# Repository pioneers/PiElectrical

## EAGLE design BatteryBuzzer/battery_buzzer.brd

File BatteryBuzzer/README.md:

#Battery Buzzer

Reacts the how angry the battery is

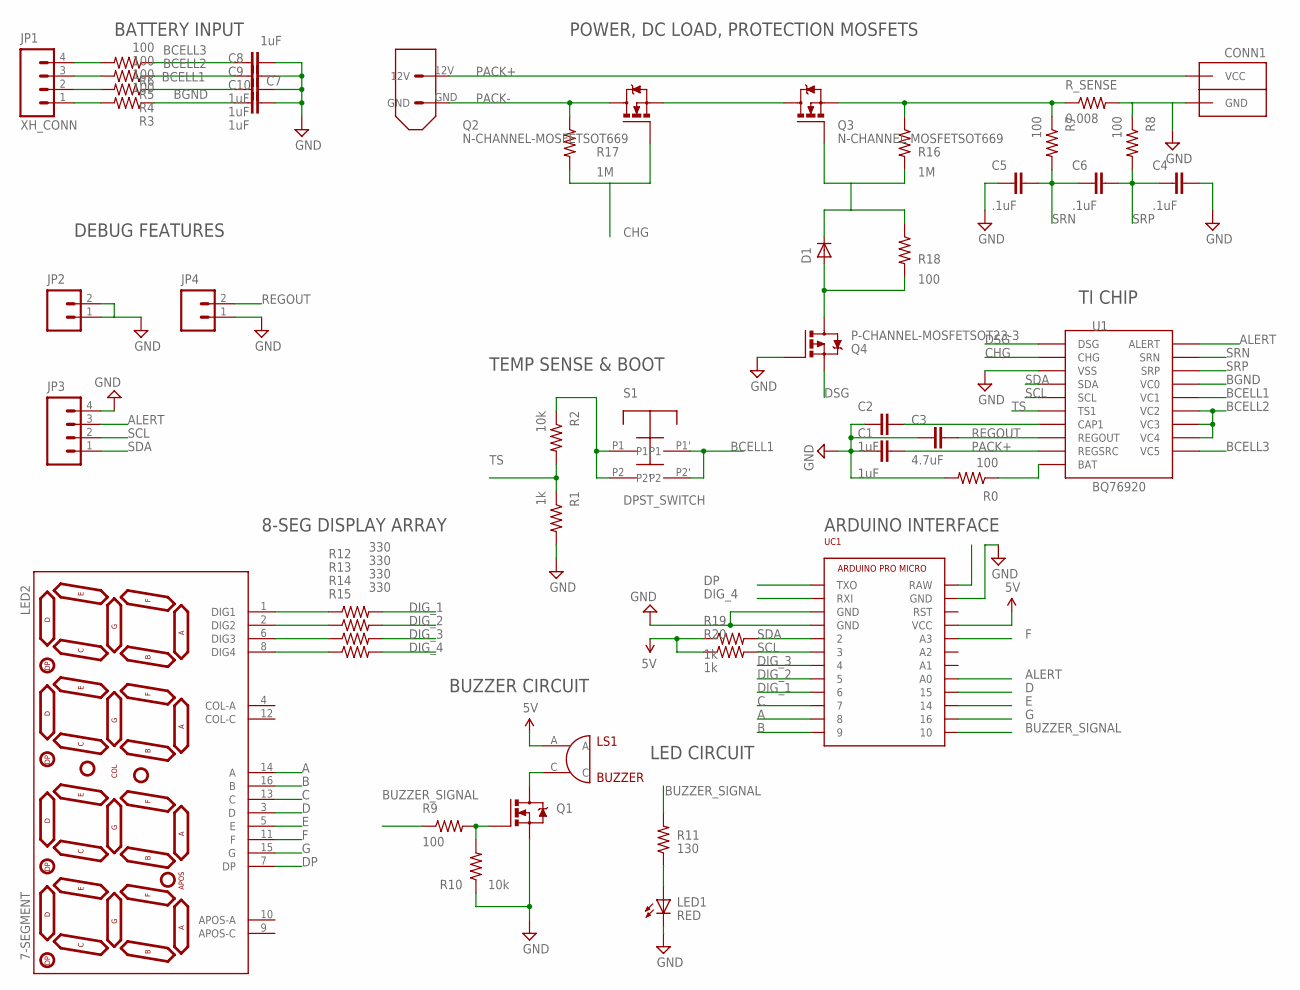
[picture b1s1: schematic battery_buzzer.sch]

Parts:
C1, C2, C7, C8, C9, C10: 1uF; 0603-CAP
C3: 4.7uF; 0603-CAP
C4, C5, C6: .1uF; 0603-CAP
CONN1: ANDERSONVERTICAL; ANDERSON_VERTICAL
D1: DIODESOD-323; SOD-323
JP1: XH_CONN; XH_CONNECTOR_4POS_2.5MM
JP2, JP4: M02PTH; 1X02
JP3: M04PTH; 1X04
LED1: RED; LED-0805
LED2: 7-SEGMENT; 7-SEGMENT-4DIGIT-YOUNGSUN
LS1: BUZZER; BUZZER_MAGNETIC_5V_12MM_RADIAL
Q1: IRFML8244; SOT23-3
Q2, Q3: N-CHANNEL-MOSFETSOT669; SOT669
Q4: P-CHANNEL-MOSFETSOT23-3; SOT23-3
R0, R3, R4, R5, R6, R7, R8, R9, R18: 100; R0603
R1, R19, R20: 1k; R0603
R2, R10: 10k; R0603
R11: 130; R0603
R12, R13, R14, R15: 330; R0603
R16, R17: 1M; R0603
R_SENSE: 0.008; V235/17
S1: DPST_SWITCH; C&K_SWITCH
U1: BQ76920; 20-TSSOP
U$1: XT60CONNECTOR
UC1: ARDUINO_PRO_MICRO

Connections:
5V: LS1.A, R19.1, R20.1, UC1.VCC
A: LED2.14 (A), UC1.8
ALERT: JP3.3, U1.P$20 (ALERT), UC1.A0
B: LED2.16 (B), UC1.9
BCELL1: C9.1, R4.1, S1.P1', S1.P2', U1.P$16 (VC1)
BCELL2: C8.1, R5.1, U1.P$13 (VC4), U1.P$14 (VC3), U1.P$15 (VC2)
BCELL3: C7.2, R6.1, U1.P$12 (VC5)
BGND: C10.1, R3.1, U1.P$17 (VC0)
BUZZER_SIGNAL: R9.1, R11.2, UC1.10
C: LED2.13 (C), UC1.7
CHG: Q2.4 (G), R17.2, U1.P$2 (CHG)
D: LED2.3 (D), UC1.15
DIG_1: R12.2, UC1.6
DIG_2: R13.2, UC1.5
DIG_3: R14.2, UC1.4
DIG_4: R15.2, UC1.RXI
DP: LED2.7 (DP), UC1.TXO
DSG: Q4.2 (S), U1.P$1 (DSG)
E: LED2.5 (E), UC1.14
F: LED2.11 (F), UC1.A3
G: LED2.15 (G), UC1.16
GND: C1.1, C2.1, C3.1, C4.2, C5.1, C7.1, C8.2, C9.2, C10.2, CONN1.PIN1 (GND), JP2.1, JP2.2, JP3.4, JP4.1, LED1.C, Q1.2 (S), Q4.1 (G), R0.2, R1.2, R8.1, R10.1, R_SENSE.2, U1.P$3 (VSS), UC1.GND@0 (GND), UC1.GND@1 (GND), UC1.GND@2 (GND)
unnamed: R0.1, U1.P$10 (BAT)
unnamed: C2.2, U1.P$7 (CAP1)
unnamed: JP1.1, R3.2
unnamed: JP1.2, R4.2
unnamed: LS1.C, Q1.3 (D)
unnamed: Q1.1 (G), R9.2, R10.2
unnamed: LED1.A, R11.1
unnamed: R2.1, S1.P1, S1.P2
unnamed: LED2.1 (DIG1), R12.1
unnamed: JP1.3, R5.2
unnamed: LED2.2 (DIG2), R13.1
unnamed: JP1.4, R6.2
unnamed: LED2.6 (DIG3), R14.1
unnamed: Q2.1 (S), Q2.2 (S), Q2.3 (S), Q3.MB (D)
unnamed: LED2.8 (DIG4), R15.1
unnamed: Q3.1 (S), Q3.2 (S), Q3.3 (S), R7.1, R16.1, R_SENSE.1
unnamed: D1.1 (A), Q4.3 (D), R18.2
unnamed: D1.2 (C), Q3.4 (G), R16.2, R18.1
PACK+: C1.2, CONN1.PIN2 (VCC), U1.P$9 (REGSRC), U$1.12V
PACK-: Q2.MB (D), R17.1, U$1.GND
RAW: UC1.RAW
REGOUT: C3.2, JP4.2, U1.P$8 (REGOUT)
SCL: JP3.2, R20.2, U1.P$5 (SCL), UC1.3
SDA: JP3.1, R19.2, U1.P$4 (SDA), UC1.2
SRN: C5.2, C6.1, R7.2, U1.P$19 (SRN)
SRP: C4.1, C6.2, R8.2, U1.P$18 (SRP)
TS: R1.1, R2.2, U1.P$6 (TS1)

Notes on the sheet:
ARDUINO INTERFACE
LED CIRCUIT
BUZZER CIRCUIT
BATTERY INPUT
8-SEG DISPLAY ARRAY
DEBUG FEATURES
TEMP SENSE & BOOT
POWER, DC LOAD, PROTECTION MOSFETS
TI CHIP

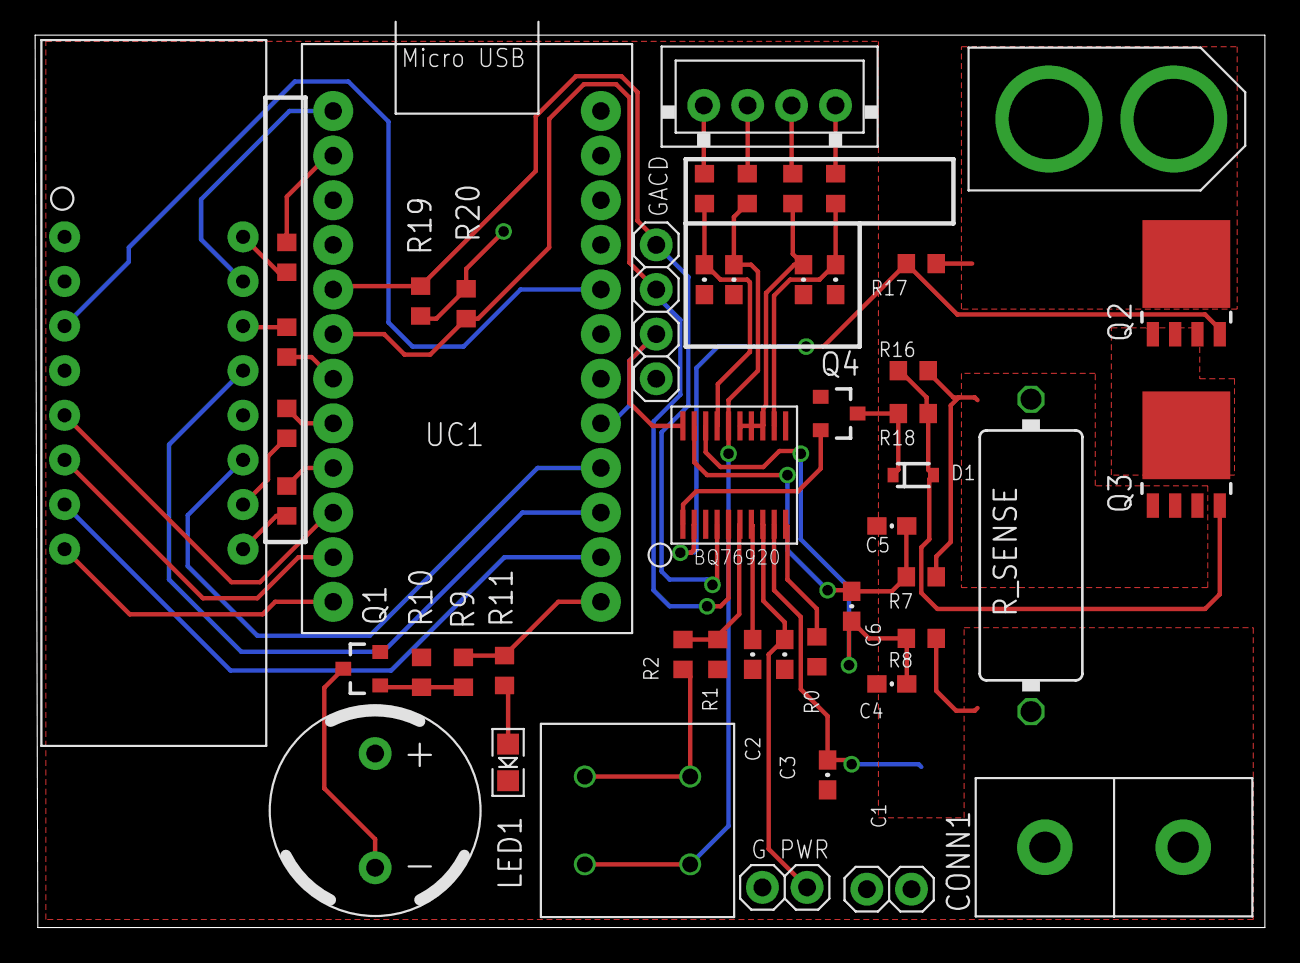
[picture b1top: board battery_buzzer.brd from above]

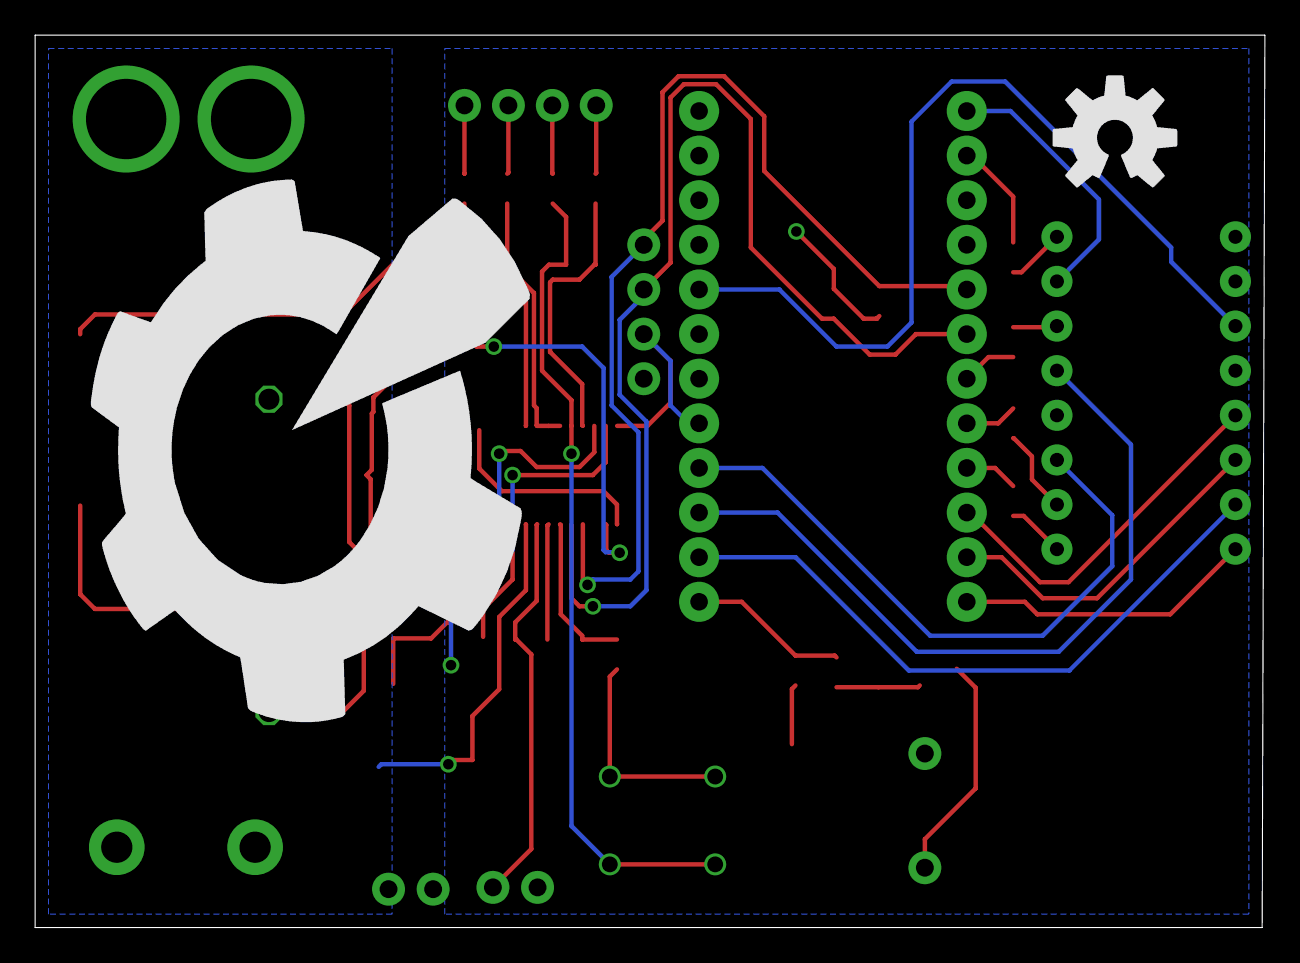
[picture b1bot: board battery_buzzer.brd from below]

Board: 2 copper layers, 70.0 x 50.8 mm, 51 parts (2 on the bottom side), 48 nets.

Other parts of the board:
U$2: OSHW-LOGO-L
U$4: PIE-LOGO

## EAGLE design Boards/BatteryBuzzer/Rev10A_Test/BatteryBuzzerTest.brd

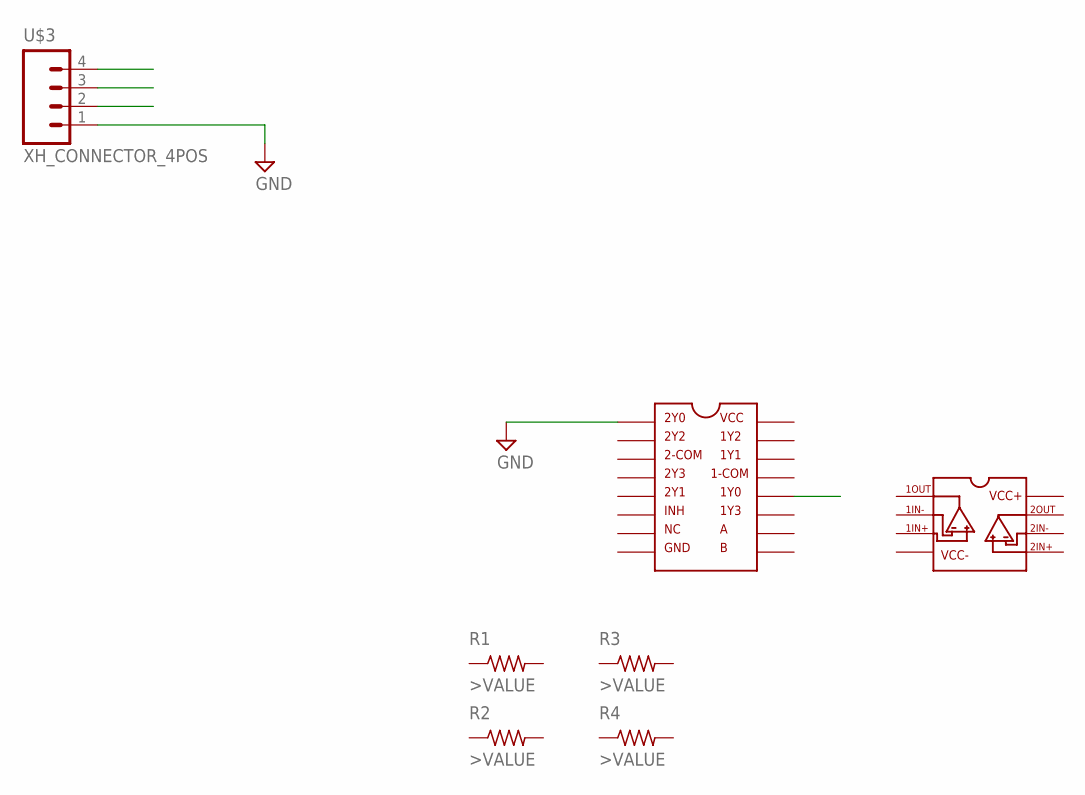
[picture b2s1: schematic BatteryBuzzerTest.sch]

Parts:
R1, R2, R3, R4: >VALUE; R0603
U$1: SN74HC4852; DIL16
U$2: TL072; DIL08
U$3: XH_CONNECTOR_4POS; XH_CONNECTOR_4POS_2.5MM

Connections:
BCELL1: U$1.12 (1Y0), U$3.2
BCELL2: U$3.3
BCELL3: U$3.4
GND: U$1.1 (2Y0), U$3.1

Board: 2 copper layers, 7 parts (0 on the bottom side), 2 nets, no tracks yet.

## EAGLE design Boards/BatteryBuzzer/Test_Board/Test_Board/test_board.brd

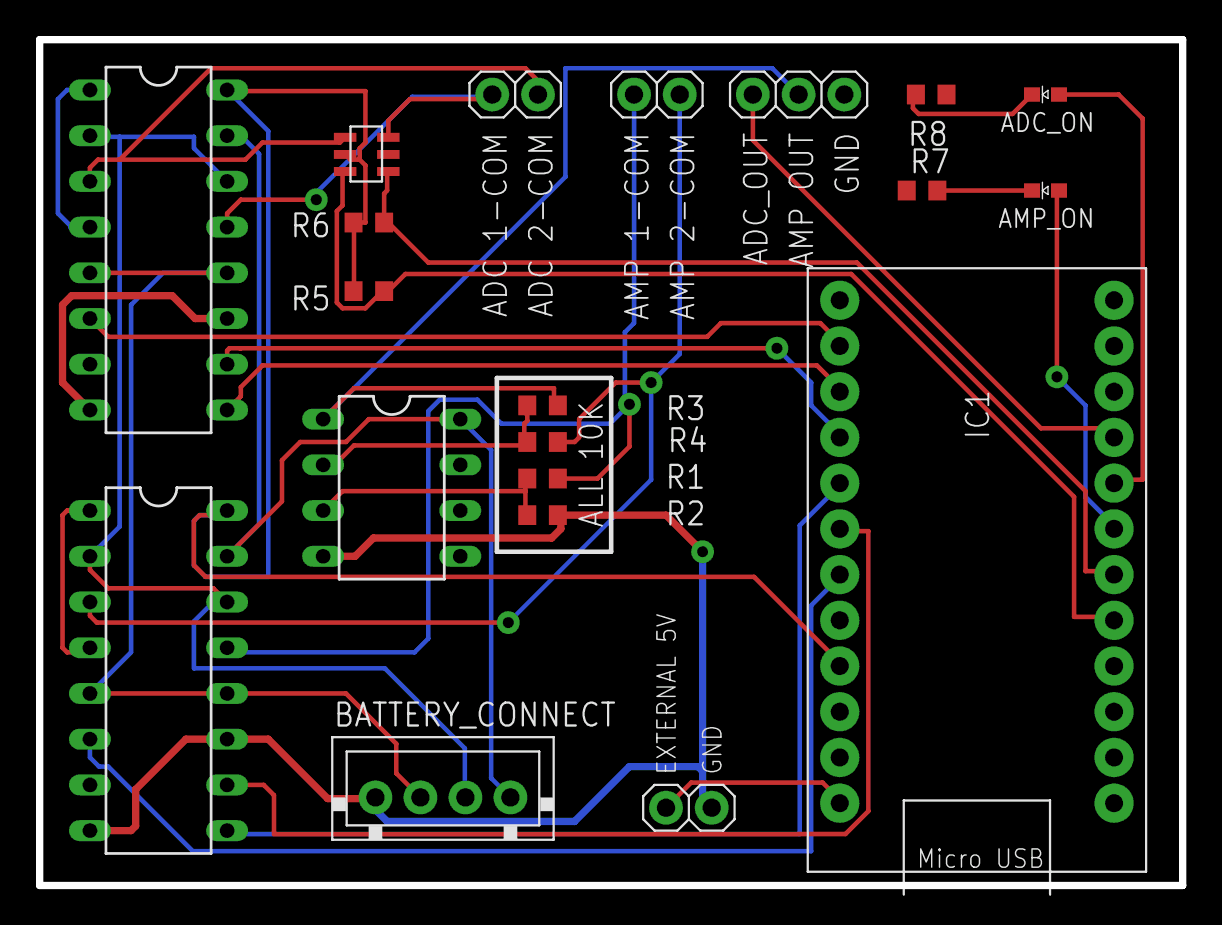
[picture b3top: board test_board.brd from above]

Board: 2 copper layers, 63.5 x 47.0 mm, 21 parts (1 on the bottom side), 26 nets.

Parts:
ADC_INPUTS: 1X02
ADC_ON: GREEN; LED-0603
AMP_ON: GREEN; LED-0603
BATTERY_CONNECT: XH_CONNECTOR_4POS; XH_CONNECTOR_4POS_2.5MM
EXTERNAL_POWER: 1X02
IC1: ARDUINO_PRO_MICRO
MUX_INPUTS: 1X02
OUTPUT: 1X03
R1, R2, R3, R4, R5, R6: 10k; R0603
R7, R8: 330; R0603
U$1, U$5: SN74HC4852; DIL16
U$2: TL072; DIL08
U$3: SOT-23_6PIN
U$7: PIE-LOGO-SMALL

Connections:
1-COM: MUX_INPUTS.2, R1.1, U$1.13
2-COM: MUX_INPUTS.1, R4.2, U$1.3
5V: EXTERNAL_POWER.2, IC1.RAW
A: IC1.A1, U$1.10
ADC_1-COM: ADC_INPUTS.2, U$3.P$1, U$5.13
ADC_2-COM: ADC_INPUTS.1, U$3.P$4, U$5.3
ADC_A: IC1.15, U$5.10
ADC_B: IC1.14, U$5.9
ADC_INH: IC1.16, U$5.6
ADC_OUT: IC1.6, OUTPUT.3
AMP_OUT: OUTPUT.2, R3.1, U$2.1
B: IC1.A0, U$1.9
BCELL1: BATTERY_CONNECT.2, U$1.5, U$1.12, U$5.5, U$5.12
BCELL2: BATTERY_CONNECT.3, U$1.2, U$1.14, U$5.2, U$5.14
BCELL3: BATTERY_CONNECT.4, U$1.15, U$2.8, U$5.15
GND: BATTERY_CONNECT.1, EXTERNAL_POWER.1, IC1.GND@0, IC1.GND@1, IC1.GND@2, OUTPUT.1, R2.1, R7.1, R8.1, U$1.1, U$1.4, U$1.8, U$1.11, U$2.4, U$3.P$2, U$5.1, U$5.4, U$5.8, U$5.11
INH_CONTROL: IC1.A2, U$1.6
LED_1: AMP_ON.A, IC1.4
LED_2: ADC_ON.A, IC1.5
unnamed: R1.2, R2.2, U$2.3
unnamed: R3.2, R4.1, U$2.2
unnamed: ADC_ON.C, R8.2
unnamed: AMP_ON.C, R7.2
SCL: IC1.3, R6.1, U$3.P$3
SDA: IC1.2, R5.1, U$3.P$6
VCC: IC1.VCC, R5.2, R6.2, U$1.16, U$3.P$5, U$5.16

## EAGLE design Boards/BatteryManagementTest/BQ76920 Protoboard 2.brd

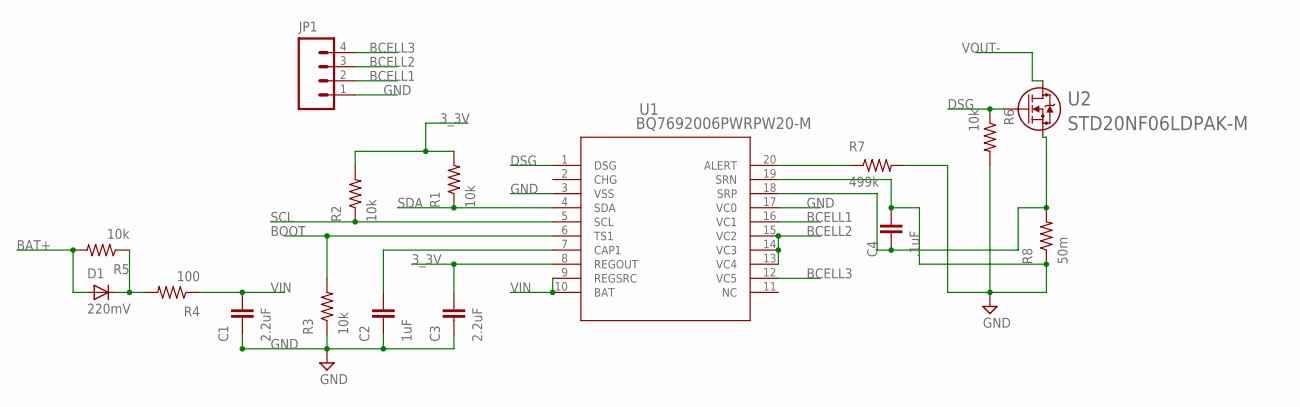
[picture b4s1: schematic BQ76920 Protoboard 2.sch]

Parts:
C1, C3: 2.2uF; 0603-CAP
C2: 1uF; 0603-CAP
C4: .1uF; 0603-CAP
D1: 220mV; SOD-323
JP1: M041X04-MTA; 1X04-MTA
R1, R2, R3, R5, R6: 10k; R0603
R4: 100; R0603
R7: 499k; R0603
R8: 50m; R2512
U1: BQ7692006PWRPW20-M; PW20-M
U2: STD20NF06LDPAK-M; DPAK-M

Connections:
3_3V: C3.2, R1.2, R2.2, U1.8 (REGOUT)
ALERT: R7.1, U1.20 (ALERT)
BAT+: D1.1 (A), R5.2
BCELL1: JP1.2, U1.16 (VC1)
BCELL2: JP1.3, U1.13 (VC4), U1.14 (VC3), U1.15 (VC2)
BCELL3: JP1.4, U1.12 (VC5)
BOOT: R3.2, U1.6 (TS1)
CAP1: C2.2, U1.7 (CAP1)
DSG: R6.1, U1.1 (DSG), U2.1
GND: C1.1, C2.1, C3.1, C4.2, JP1.1, R3.1, R6.2, R7.2, R8.1, U1.3 (VSS), U1.17 (VC0), U1.19 (SRN)
unnamed: D1.2 (C), R4.2, R5.1
SCL: R2.1, U1.5 (SCL)
SDA: R1.1, U1.4 (SDA)
SOURCE: C4.1, R8.2, U1.18 (SRP), U2.2 (3)
VIN: C1.2, R4.1, U1.9 (REGSRC), U1.10 (BAT)
VOUT-: U2.3 (2)

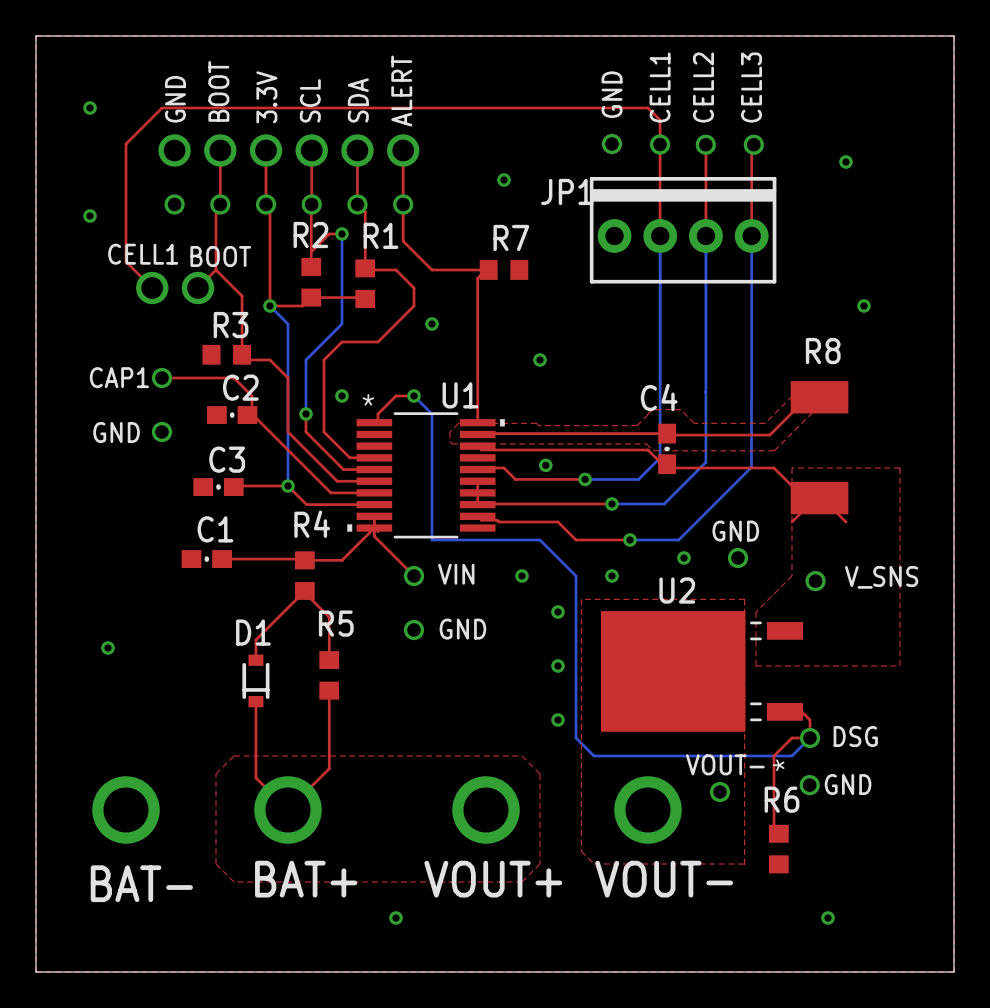
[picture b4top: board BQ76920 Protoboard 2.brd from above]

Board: 2 copper layers, 51.0 x 52.0 mm, 16 parts (0 on the bottom side), 15 nets.

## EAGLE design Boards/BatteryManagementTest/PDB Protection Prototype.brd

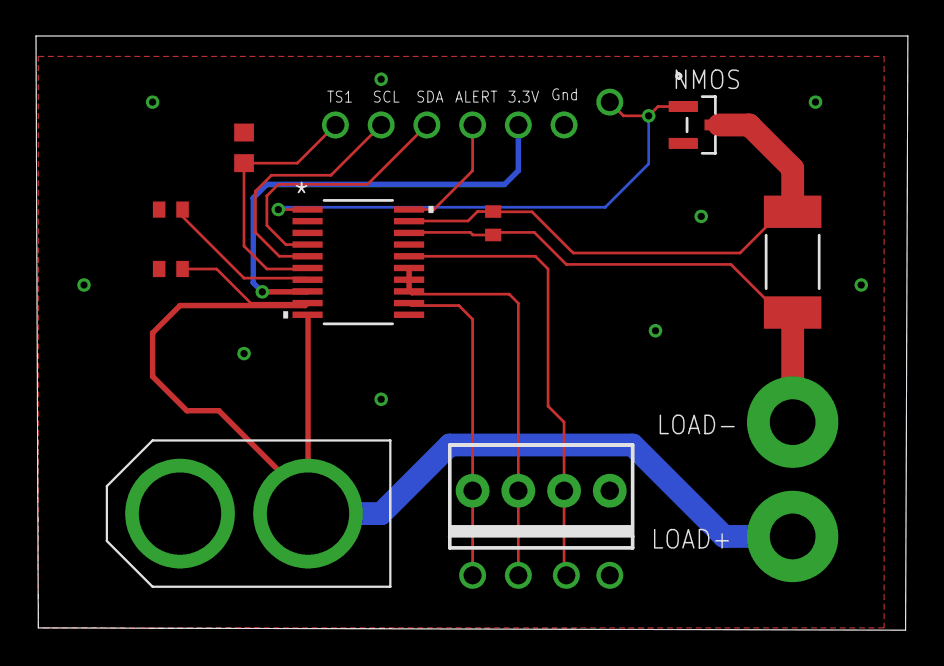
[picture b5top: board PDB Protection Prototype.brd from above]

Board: 2 copper layers, 48.4 x 33.0 mm, 9 parts (0 on the bottom side), 10 nets.

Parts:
C1, C2: 1uF; C0402
C3: .1uF; C0402
JP1: 1X04-MTA
R_SHUNT: 70m; R2512
R_TS: 10k; R0603
U1: BQ7692000PWR; PW20
U2: DMN6140L-13SOT-23-M; SOT-23-M
U$1: XT60CONNECTOR

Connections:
BCELL1: JP1.2, U1.16
BCELL2: JP1.3, U1.13, U1.14, U1.15
BCELL3: JP1.4, U1.12
DSG: U1.1, U2.1
GND: C1.2, C2.2, JP1.1, R_TS.1, U1.3, U1.17, U2.2, U$1.GND
LOAD-: C3.1, R_SHUNT.1, U1.18
unnamed: C3.2, R_SHUNT.2, U1.19, U2.3
unnamed: C1.1, U1.7
TS1: R_TS.2, U1.6
VBAT: C2.1, U1.9, U1.10, U$1.12V

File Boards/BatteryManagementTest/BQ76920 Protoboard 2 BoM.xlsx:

Reference Designator | Description | Manufacturer | Manufacturer Part Number | Distributor | Distributor Part Number
U1 | Battery Protection IC | Texas Instruments | BQ7692006PWR | Digikey | 296-39960-1-ND
C1, C2 | 1uF Capacitor
C3 | .1uF Capacitor |  | CL05A104MP5NNNC | Digikey | 1276-1443-1-ND
R_SHUNT | 5m Shunt | Bourns Inc. | CRE2512-FZ-R005E-3 | Digikey | CRE2512-FZ-R005E-3CT-ND
U2 | Power N-Channel Mosfet | STMicroelectronics | STD20NF06LAG | Digikey | 497-17143-1-ND

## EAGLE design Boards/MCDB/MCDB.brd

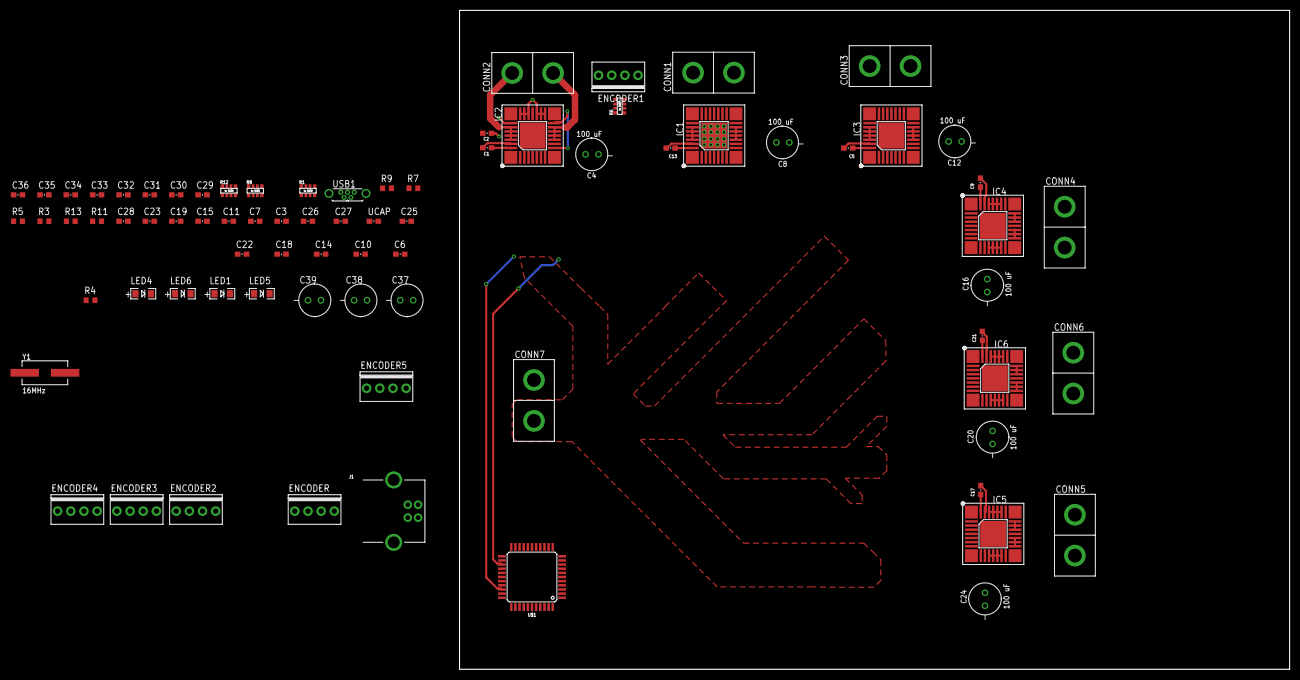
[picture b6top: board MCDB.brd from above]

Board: 2 copper layers, 160.0 x 127.0 mm, 78 parts (0 on the bottom side), 63 nets.

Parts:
C1, C5, C9, C13, C17, C21: 33 nF; 0603-CAP
C2, C6, C10, C14, C18, C22: 100 nF; 0603-CAP
C3, C7, C11, C15, C19, C23, C28: 1 uF; 0603-CAP
C4, C8, C12, C16, C20, C24: 100 uF; .248"CAP_THRU
C25: 22 pF; 0603-CAP
C26: 22pF; 0603-CAP
C27: .1 uF; 0603-CAP
C29, C30, C31, C32, C33, C34, C35, C36: 0603-CAP
C37, C38, C39: .248"CAP_THRU
CONN1, CONN2, CONN3, CONN4, CONN5, CONN6, CONN7: ANDERSONVERTICAL; ANDERSON_VERTICAL
ENCODER, ENCODER1, ENCODER2, ENCODER3, ENCODER4, ENCODER5: 1X04-MTA
IC1, IC2, IC3, IC4, IC5, IC6: MC33926; PQFN-32
J1: USB_B_PTH; USB-B-PTH
LED1, LED6: GREEN; LED-1206
LED4: RED; LED-1206
LED5: YELLOW; LED-1206
R1, R6, R12: 10k; 4X-0603
R3, R5, R7, R9, R11, R13: 200; R0603
R4: >VALUE; R0603
R8: 330; 4X-0603
U$1: 32U4; TQFP44
UCAP: 1 uF; 0603-CAP
USB1: USB-OTGMICRO-AB-VERT; USB-MICRO-AB-VERT
Y1: 16MHz; CRYSTAL-SMD-7.6X4.1-2PIN

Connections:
A1: ENCODER3.3, R1.5, U$1.36
A2: ENCODER.3, R1.7, U$1.37
A3: ENCODER1.3, R6.5, U$1.38
A4: ENCODER2.3, R6.7, U$1.39
A5: ENCODER4.3, R12.5, U$1.40
A6: ENCODER5.3, R12.7, U$1.41
B1: ENCODER3.4, R1.6, U$1.9
B2: ENCODER.4, R1.8, U$1.10
B3: ENCODER1.4, R6.6, U$1.11
B4: ENCODER2.4, R6.8, U$1.28
B5: ENCODER4.4, R12.6, U$1.19
B6: ENCODER5.4, R12.8, U$1.20
CCP: C13.1, IC1.32
CCP2: C1.1, IC2.32
CCP3: C5.1, IC3.32
CCP4: C9.1, IC4.32
CCP5: C17.1, IC5.32
CCP6: C21.1, IC6.32
D+: C29.2, J1.D+, U$1.4, USB1.P$3
D-: C30.2, J1.D-, U$1.3, USB1.P$2
FB1: C15.2, IC1.8, R9.2
FB2: C3.2, IC2.8, R3.2
FB3: C7.2, IC3.8, R5.2
FB4: C11.2, IC4.8, R7.2
FB5: C19.2, IC5.8, R11.2
FB6: C23.2, IC6.8, R13.2
GND: C2.1, C3.1, C4.MINUS, C6.1, C7.1, C8.MINUS, C10.1, C11.1, C12.MINUS, C14.1, C15.1, C16.MINUS, C18.1, C19.1, C20.MINUS, C22.1, C23.1, C24.MINUS, C25.1, C26.1, C27.1, C28.1, C29.1, C30.1, C31.1, C32.1, C33.1, C34.1, C35.1, C36.1, C37.MINUS, C38.MINUS, C39.MINUS, CONN7.PIN2, ENCODER.2, ENCODER1.2, ENCODER2.2, ENCODER3.2, ENCODER4.2, ENCODER5.2, IC1.3, IC1.5, IC1.18, IC1.19, IC1.20, IC1.22, IC1.23, IC1.24, IC1.26, IC1.MID, IC2.3, IC2.5, IC2.18, IC2.19, IC2.20, IC2.22, IC2.23, IC2.24, IC2.26, IC2.MID, IC3.3, IC3.5, IC3.18, IC3.19, IC3.20, IC3.22, IC3.23, IC3.24, IC3.26, IC3.MID, IC4.3, IC4.5, IC4.18, IC4.19, IC4.20, IC4.22, IC4.23, IC4.24, IC4.26, IC4.MID, IC5.3, IC5.5, IC5.18, IC5.19, IC5.20, IC5.22, IC5.23, IC5.24, IC5.26, IC5.MID, IC6.3, IC6.5, IC6.18, IC6.19, IC6.20, IC6.22, IC6.23, IC6.24, IC6.26, IC6.MID, J1.GND, R3.1, R5.1, R7.1, R8.2, R8.3, R8.4, R9.1, R11.1, R13.1, U$1.5, U$1.15, U$1.23, U$1.33, U$1.35, U$1.43, UCAP.1, USB1.P$5, USB1.P$6, USB1.P$7
INV1: IC1.7, U$1.21
INV2: IC2.7, U$1.25
INV3: IC3.7, U$1.1
INV4: IC4.7, U$1.26
INV5: IC5.7, U$1.32
INV6: IC6.7, U$1.8
unnamed: LED4.C, R8.5
unnamed: LED6.C, R8.7
unnamed: LED5.C, R8.6
unnamed: LED1.C, R8.8
unnamed: U$1.6, UCAP.2
unnamed: C25.2, U$1.17, Y1.P$2
unnamed: C26.2, U$1.16, Y1.P$1
unnamed: C27.2, U$1.42
unnamed: R4.1, U$1.13
OUT1: CONN1.PIN1, IC1.12, IC1.13, IC1.14, IC1.15
OUT2: CONN1.PIN2, IC1.27, IC1.28, IC1.29, IC1.30
OUT3: CONN2.PIN1, IC2.12, IC2.13, IC2.14, IC2.15
OUT4: CONN2.PIN2, IC2.27, IC2.28, IC2.29, IC2.30
OUT5: CONN3.PIN1, IC3.12, IC3.13, IC3.14, IC3.15
OUT6: CONN3.PIN2, IC3.27, IC3.28, IC3.29, IC3.30
OUT7: CONN4.PIN1, IC4.12, IC4.13, IC4.14, IC4.15
OUT8: CONN4.PIN2, IC4.27, IC4.28, IC4.29, IC4.30
OUT9: CONN5.PIN1, IC5.12, IC5.13, IC5.14, IC5.15
OUT10: CONN5.PIN2, IC5.27, IC5.28, IC5.29, IC5.30
OUT11: CONN6.PIN1, IC6.12, IC6.13, IC6.14, IC6.15
OUT12: CONN6.PIN2, IC6.27, IC6.28, IC6.29, IC6.30
PD5: R8.1, U$1.22
PWM1: IC1.2, U$1.18
PWM2: IC2.2, U$1.31
PWM3: IC3.2, U$1.27
PWM4: IC4.2, U$1.29
PWM5: IC5.2, U$1.30
PWM6: IC6.2, U$1.12
VCC: C28.2, C31.2, C32.2, C33.2, C34.2, C35.2, C36.2, ENCODER.1, ENCODER1.1, ENCODER2.1, ENCODER3.1, ENCODER4.1, ENCODER5.1, IC1.1, IC1.10, IC1.16, IC2.1, IC2.10, IC2.16, IC3.1, IC3.10, IC3.16, IC4.1, IC4.10, IC4.16, IC5.1, IC5.10, IC5.16, IC6.1, IC6.10, IC6.16, J1.VBUS, LED1.A, R1.1, R1.2, R1.3, R1.4, R4.2, R6.1, R6.2, R6.3, R6.4, R12.1, R12.2, R12.3, R12.4, U$1.2, U$1.7, U$1.14, U$1.24, U$1.34, U$1.44, USB1.P$1
VPWR: C1.2, C2.2, C4.PLUS, C5.2, C6.2, C8.PLUS, C9.2, C10.2, C12.PLUS, C13.2, C14.2, C16.PLUS, C17.2, C18.2, C20.PLUS, C21.2, C22.2, C24.PLUS, C37.PLUS, C38.PLUS, C39.PLUS, CONN7.PIN1, IC1.4, IC1.6, IC1.11, IC1.31, IC2.4, IC2.6, IC2.11, IC2.31, IC3.4, IC3.6, IC3.11, IC3.31, IC4.4, IC4.6, IC4.11, IC4.31, IC5.4, IC5.6, IC5.11, IC5.31, IC6.4, IC6.6, IC6.11, IC6.31

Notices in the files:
parts and their libraries:
SparkFun-Connectors: Licensing: Creative Commons ShareAlike 4.0 International - https://creativecommons.org/licenses/by-sa/4.0
